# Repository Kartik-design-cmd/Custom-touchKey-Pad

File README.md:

Custom Touch Key Pad — MIDI Keypad PCB

A custom-designed MIDI keypad PCB created using KiCad. This project combines capacitive touch controls, physical input components, and an ESP32-S3 microcontroller to create a compact controller intended for use with MIDI-compatible music software.

Project status: PCB design completed.

Project Overview

The goal of this project was to design a custom MIDI keypad from its electrical schematic through its printed circuit board layout. The design brings multiple input controls together on one PCB, allowing the device to send musical control inputs to compatible software.

The PCB was designed in KiCad, including the schematic, component footprints, board outline, and routed connections. Special attention was given to component placement and trace routing to create a more organized layout.

Features and Components

The design incorporates the following components and features:

- ESP32-S3 microcontroller: The controller intended to process inputs and communicate with compatible MIDI software.
- Capacitive touch pads: Touch-sensitive inputs intended to trigger musical notes.
- Rotary encoder: A rotary input for controlling a parameter.
- Slider potentiometers: Physical controls intended for continuous MIDI parameter adjustments.
- RGB LEDs: Visual feedback using addressable LEDs.
- Custom PCB layout: A board designed to accommodate the components and their electrical connections.

The intended MIDI workflow is for the keypad to send control messages to a compatible host device, such as a computer or Android phone or tablet. The host's MIDI-compatible software generates the sound; the PCB itself does not require a built-in speaker.

Design Process

1. Schematic and Footprint Assignment

The project began with creating the electrical schematic in KiCad and assigning footprints to the components. This established the electrical connections and the physical component layouts needed for PCB design.

One of the main challenges was creating a custom footprint for the capacitive touch pads. My initial attempts did not transfer correctly into the PCB Editor, so I recreated the footprint several times and used online tutorials to troubleshoot the problem. I eventually resolved the issue and successfully incorporated the footprint into the PCB design.

2. PCB Outline and Layout

After completing the schematic and footprint assignments, I moved to the PCB Editor and drew the board outline using the "Edge.Cuts" layer.

I then began placing the components and routing the electrical connections. The first routing attempt produced multiple design-rule errors, so I reviewed the layout and adjusted the component positions.

3. Routing and Layout Improvements

Routing the PCB was one of the most time-consuming parts of the project. Some connections were difficult to route cleanly, and certain traces were too close together. Rather than making only small adjustments, I reorganized much of the component placement, moving components around the board to improve the routing paths and make the layout more organized.

After several hours of routing and rearranging components, I completed the board's trace routing and reduced the remaining design-rule issues. I also compared the remaining checks with the project guide to understand which reported issues were expected for this design.

<!-- ADD PICTURE 3 HERE: Add a screenshot of the final routed PCB, with the traces clearly visible. -->"Final routed PCB" (images/pcb-routed.png)

4. Three-Dimensional PCB View

The PCB design can also be inspected using KiCad's 3D Viewer. This view helps visualize the board and the placement of components in three dimensions, rather than only as a flat layout.

Software and Tools

- KiCad: Electrical schematic, footprint assignment, PCB layout, routing, and 3D visualization.
- ESP32-S3: Microcontroller selected for the keypad design.

Challenges and What I Learned

This project gave me practical experience with the PCB design process, from schematic creation to board layout and routing.

The most significant challenge was getting the custom capacitive touch-pad footprint working correctly. I learned that a footprint must be properly created and available to the PCB Editor before it can be used in the board layout.

I also learned how strongly component placement affects PCB routing. My first layout resulted in many design-rule errors, but rearranging the components created better routing paths and a cleaner board. This taught me to consider both electrical connections and physical layout when designing a PCB.

Working through these problems improved my understanding of KiCad, footprints, board outlines, copper traces, design-rule checks, and the relationship between a schematic and a physical PCB.

Final Result

The PCB design phase of the MIDI keypad project is complete. The schematic was created, component footprints were assigned, the board outline was drawn, and the electrical connections were routed. The layout was reorganized to improve trace routing and component placement, and the design was reviewed using KiCad's design-rule checks.

The completed design represents the PCB layout for a custom MIDI keypad with capacitive touch inputs, a rotary encoder, slider potentiometers, RGB LEDs, and an ESP32-S3 microcontroller.

This project was based on the MIDI-Keypad guide by KaiPereira.

- Original project guide: https://github.com/KaiPereira/MIDI-Keypad/blob/master/README.md

The original guide was used as a reference for the design process. The PCB layout and troubleshooting work documented here reflect my own progress through the project.

Check out my BOM and my project cost is coming along $37. I am willing to pay $7 from my pocket as long as I can get the funding of $30(or $33 with margin).

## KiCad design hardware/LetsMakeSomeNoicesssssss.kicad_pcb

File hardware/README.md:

You will find my .sch, .pro and .pcb files here

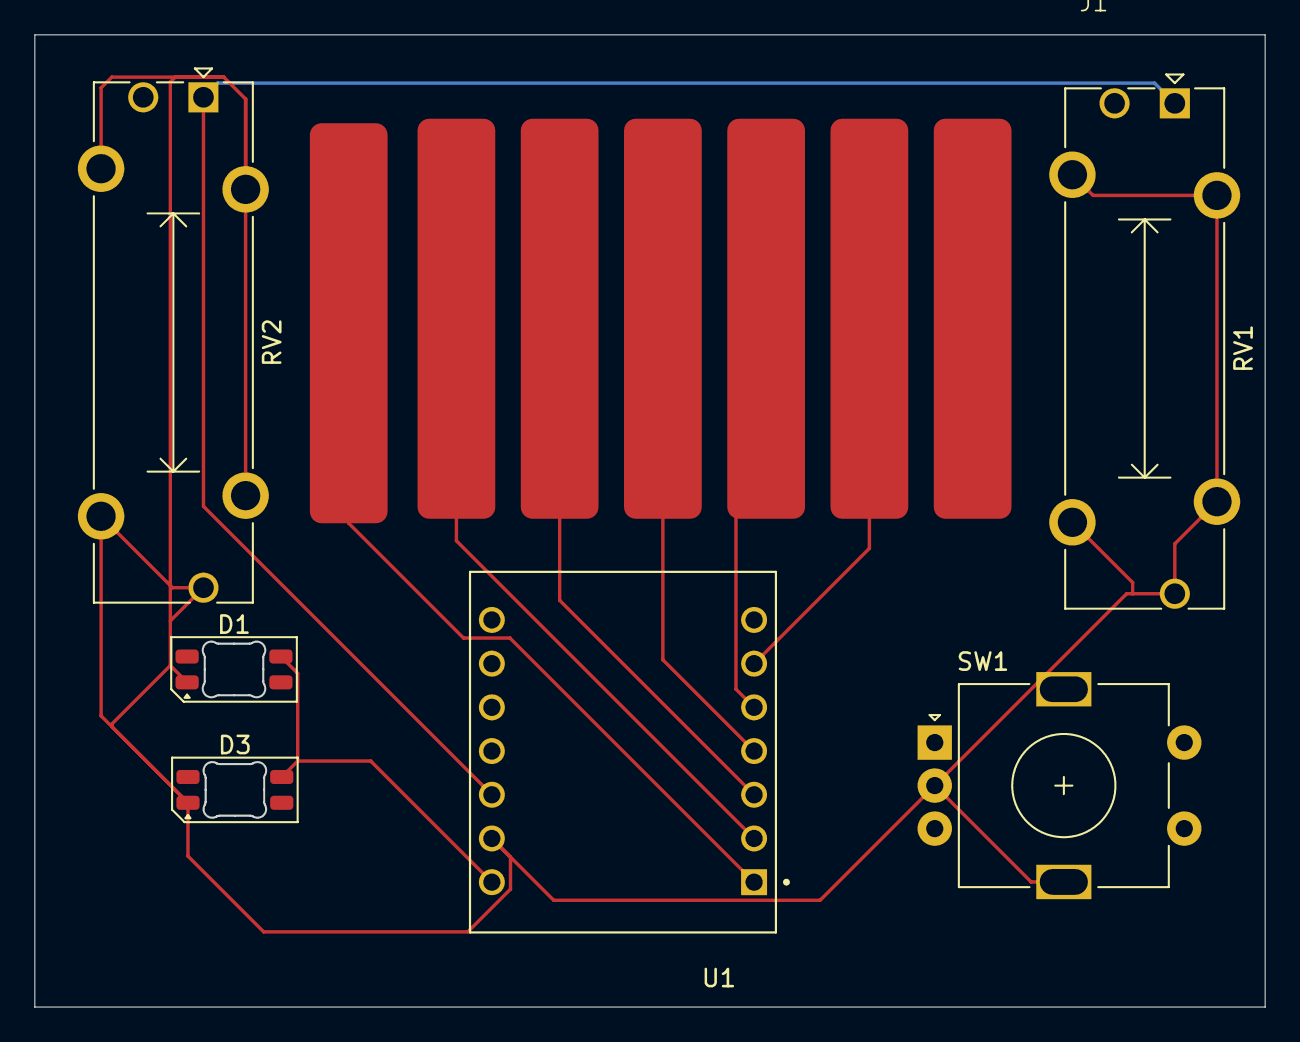
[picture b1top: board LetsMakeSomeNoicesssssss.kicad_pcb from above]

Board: 2 copper layers, 71.5 x 56.5 mm, 7 parts (0 on the bottom side), 9 nets.

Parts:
D1, D3: SK6812MINI-E; LED_SK6812MINI-E_3.2x2.8mm_P1.5mm_ReverseMount
J1: Conn_01x07; Capacitive touch buttons
RV1, RV2: Slider; Potentiometer_Bourns_PTA1543_Single_Slide
SW1: RotaryEncoder_Switch_MP; RotaryEncoder_Alps_EC11E-Switch_Vertical_H20mm
U1: XIAO-ESP32-S3; XIAO ESP32-S3

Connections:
+3V3: RV1.1, RV2.1, U1.12 (3V3)
+5V: D1.3 (VDD), D3.3 (VDD), U1.14 (5V)
/TOUCH1: J1.1, U1.1 (D0/GPIO1)
/TOUCH2: J1.2, U1.2 (D1/GPIO2)
/TOUCH3: J1.3, U1.3 (D2/GPIO3)
/TOUCH4: J1.4, U1.4 (D3/GPIO4)
/TOUCH5: J1.5, U1.5 (D4/GPIO5)
/TOUCH6: J1.6, U1.6 (D5/GPIO6)
GND: D1.1 (VSS), D3.1 (VSS), RV1.3, RV1.MP (MountPin), RV2.3, RV2.MP (MountPin), SW1.C, SW1.MP, U1.13 (GND)
